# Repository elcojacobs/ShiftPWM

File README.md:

# ShiftPWM-Redux
Arduino Library for software PWM with shift registers

This branch optimizes the SPI sending code. 

The new code is about 30% faster than the original. You can use the extra time to either have more foreground load, or to increase the PWM frequency.

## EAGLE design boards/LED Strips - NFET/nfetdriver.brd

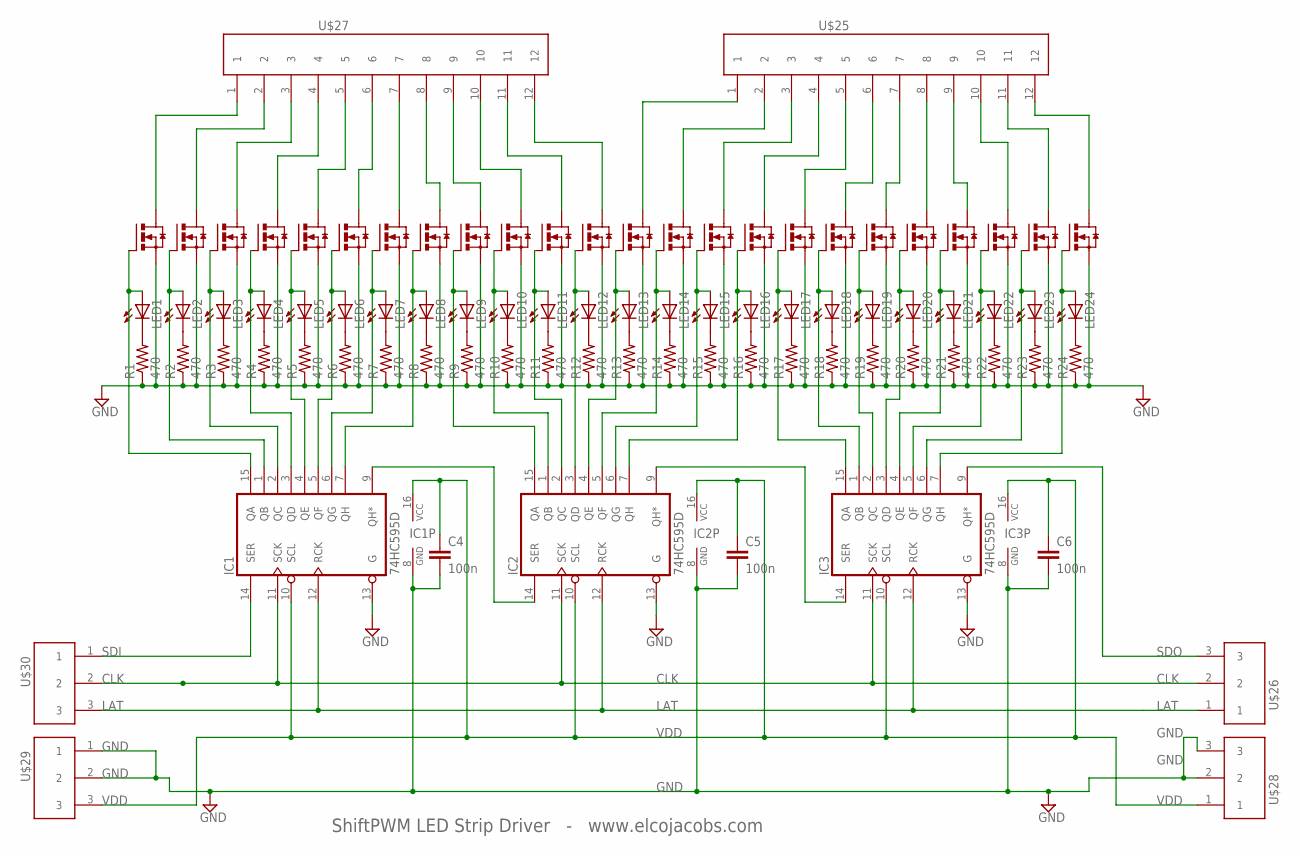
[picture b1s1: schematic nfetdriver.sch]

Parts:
C4, C5, C6: 100n; C0603
IC1, IC2, IC3: 74HC595D; SO16
LED1, LED2, LED3, LED4, LED5, LED6, LED7, LED8, LED9, LED10, LED11, LED12, LED13, LED14, LED15, LED16, LED17, LED18, LED19, LED20, LED21, LED22, LED23, LED24: LEDCHIPLED_0603; CHIPLED_0603
R1, R2, R3, R4, R5, R6, R7, R8, R9, R10, R11, R12, R13, R14, R15, R16, R17, R18, R19, R20, R21, R22, R23, R24: 470; R0603
U$1, U$2, U$3, U$4, U$5, U$6, U$7, U$8, U$9, U$10, U$11, U$12, U$13, U$14, U$15, U$16, U$17, U$18, U$19, U$20, U$21, U$22, U$23, U$24: SI2302DS; SOT23
U$25, U$27: 3.5MM12P
U$26, U$28, U$29, U$30: 3.5MM3PHORIZONTAL; 3.5MM3P

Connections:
CLK: IC1.11 (SCK), IC2.11 (SCK), IC3.11 (SCK), U$26.2, U$30.2
GND: C4.2, C5.2, C6.2, IC1.8 (GND), IC1.13 (G), IC2.8 (GND), IC2.13 (G), IC3.8 (GND), IC3.13 (G), R1.1, R2.1, R3.1, R4.1, R5.1, R6.1, R7.1, R8.1, R9.1, R10.1, R11.1, R12.1, R13.1, R14.1, R15.1, R16.1, R17.1, R18.1, R19.1, R20.1, R21.1, R22.1, R23.1, R24.1, U$1.SOURCE (S), U$2.SOURCE (S), U$3.SOURCE (S), U$4.SOURCE (S), U$5.SOURCE (S), U$6.SOURCE (S), U$7.SOURCE (S), U$8.SOURCE (S), U$9.SOURCE (S), U$10.SOURCE (S), U$11.SOURCE (S), U$12.SOURCE (S), U$13.SOURCE (S), U$14.SOURCE (S), U$15.SOURCE (S), U$16.SOURCE (S), U$17.SOURCE (S), U$18.SOURCE (S), U$19.SOURCE (S), U$20.SOURCE (S), U$21.SOURCE (S), U$22.SOURCE (S), U$23.SOURCE (S), U$24.SOURCE (S), U$28.2, U$28.3, U$29.1, U$29.2
LAT: IC1.12 (RCK), IC2.12 (RCK), IC3.12 (RCK), U$26.1, U$30.3
unnamed: IC1.9 (QH*), IC2.14 (SER)
unnamed: IC2.9 (QH*), IC3.14 (SER)
unnamed: IC1.15 (QA), LED1.A, U$1.GATE (G)
unnamed: IC1.1 (QB), LED2.A, U$2.GATE (G)
unnamed: IC1.2 (QC), LED3.A, U$3.GATE (G)
unnamed: IC1.3 (QD), LED4.A, U$4.GATE (G)
unnamed: IC1.4 (QE), LED5.A, U$5.GATE (G)
unnamed: IC1.6 (QG), LED7.A, U$7.GATE (G)
unnamed: IC1.5 (QF), LED6.A, U$6.GATE (G)
unnamed: U$1.DRAIN (D), U$27.1
unnamed: IC2.15 (QA), LED9.A, U$9.GATE (G)
unnamed: IC2.1 (QB), LED10.A, U$10.GATE (G)
unnamed: IC2.2 (QC), LED11.A, U$11.GATE (G)
unnamed: IC2.3 (QD), LED12.A, U$12.GATE (G)
unnamed: IC2.4 (QE), LED13.A, U$13.GATE (G)
unnamed: IC2.5 (QF), LED14.A, U$14.GATE (G)
unnamed: IC2.6 (QG), LED15.A, U$15.GATE (G)
unnamed: IC2.7 (QH), LED16.A, U$16.GATE (G)
unnamed: IC3.15 (QA), LED17.A, U$17.GATE (G)
unnamed: IC3.1 (QB), LED18.A, U$18.GATE (G)
unnamed: IC3.2 (QC), LED19.A, U$19.GATE (G)
unnamed: IC3.3 (QD), LED20.A, U$20.GATE (G)
unnamed: IC3.4 (QE), LED21.A, U$21.GATE (G)
unnamed: IC3.5 (QF), LED22.A, U$22.GATE (G)
unnamed: IC3.6 (QG), LED23.A, U$23.GATE (G)
unnamed: IC3.7 (QH), LED24.A, U$24.GATE (G)
unnamed: U$2.DRAIN (D), U$27.2
unnamed: U$3.DRAIN (D), U$27.3
unnamed: U$4.DRAIN (D), U$27.4
unnamed: U$5.DRAIN (D), U$27.5
unnamed: U$6.DRAIN (D), U$27.6
unnamed: U$7.DRAIN (D), U$27.7
unnamed: U$8.DRAIN (D), U$27.8
unnamed: U$9.DRAIN (D), U$27.9
unnamed: U$10.DRAIN (D), U$27.10
unnamed: U$11.DRAIN (D), U$27.11
unnamed: U$12.DRAIN (D), U$27.12
unnamed: U$13.DRAIN (D), U$25.1
unnamed: U$14.DRAIN (D), U$25.2
unnamed: IC1.7 (QH), LED8.A, U$8.GATE (G)
unnamed: U$16.DRAIN (D), U$25.4
unnamed: U$17.DRAIN (D), U$25.5
unnamed: U$18.DRAIN (D), U$25.6
unnamed: U$19.DRAIN (D), U$25.7
unnamed: U$20.DRAIN (D), U$25.8
unnamed: U$21.DRAIN (D), U$25.9
unnamed: U$22.DRAIN (D), U$25.10
unnamed: U$23.DRAIN (D), U$25.11
unnamed: U$24.DRAIN (D), U$25.12
unnamed: LED1.C, R1.2
unnamed: LED2.C, R2.2
unnamed: LED3.C, R3.2
unnamed: LED4.C, R4.2
unnamed: LED5.C, R5.2
unnamed: LED6.C, R6.2
unnamed: LED7.C, R7.2
unnamed: LED8.C, R8.2
unnamed: LED9.C, R9.2
unnamed: LED10.C, R10.2
unnamed: LED11.C, R11.2
unnamed: LED12.C, R12.2
unnamed: LED13.C, R13.2
unnamed: LED14.C, R14.2
unnamed: LED15.C, R15.2
unnamed: LED16.C, R16.2
unnamed: LED17.C, R17.2
unnamed: LED18.C, R18.2
unnamed: LED19.C, R19.2
unnamed: LED20.C, R20.2
unnamed: LED21.C, R21.2
unnamed: LED22.C, R22.2
unnamed: LED23.C, R23.2
unnamed: LED24.C, R24.2
unnamed: U$15.DRAIN (D), U$25.3
SDI: IC1.14 (SER), U$30.1
SDO: IC3.9 (QH*), U$26.3
VDD: C4.1, C5.1, C6.1, IC1.10 (SCL), IC1.16 (VCC), IC2.10 (SCL), IC2.16 (VCC), IC3.10 (SCL), IC3.16 (VCC), U$28.1, U$29.3

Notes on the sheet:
ShiftPWM LED Strip Driver - www.elcojacobs.com
SDI
SDO
VDD

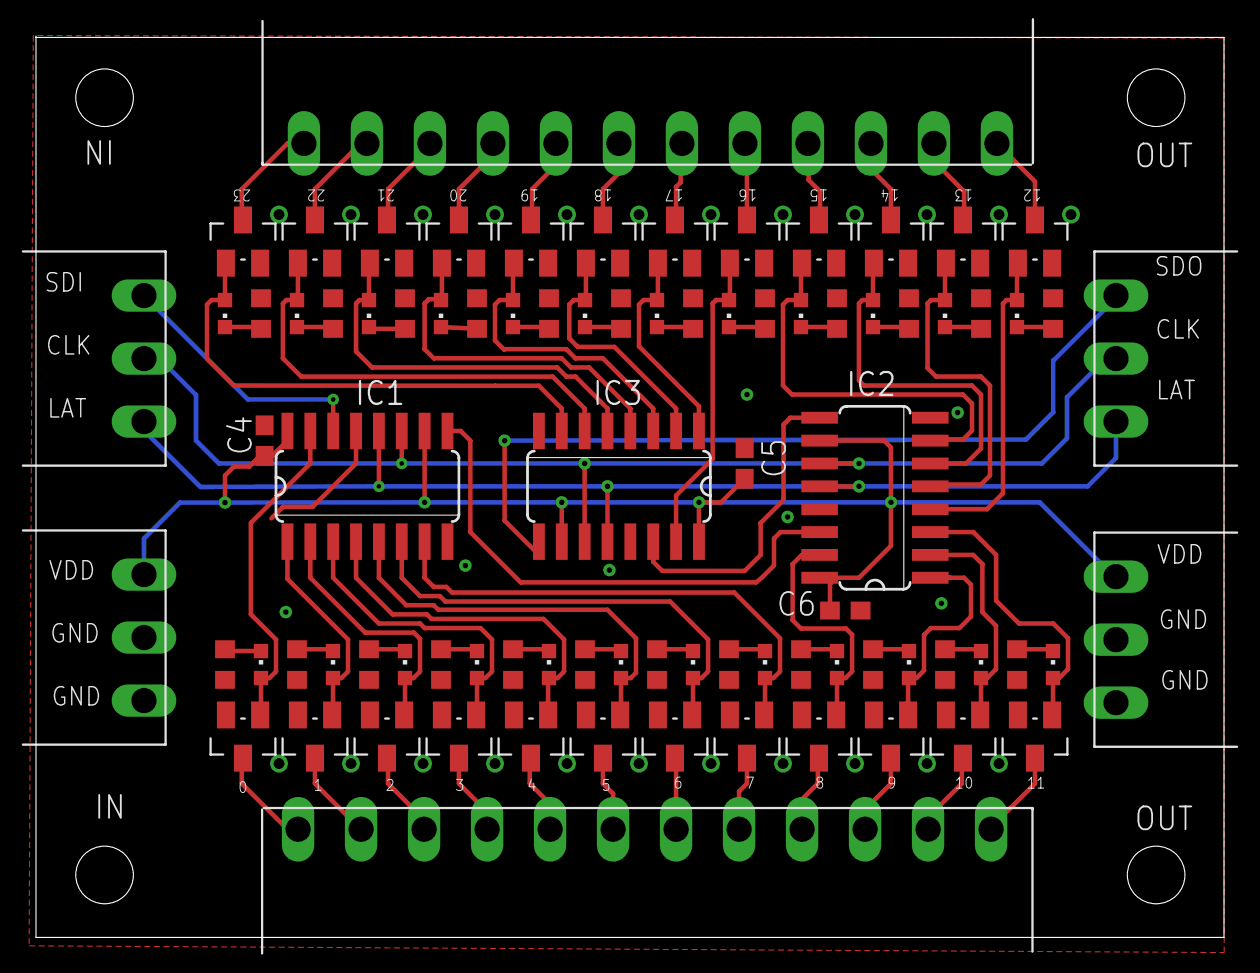
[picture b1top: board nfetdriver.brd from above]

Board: 2 copper layers, 66.0 x 50.0 mm, 84 parts (0 on the bottom side), 80 nets.

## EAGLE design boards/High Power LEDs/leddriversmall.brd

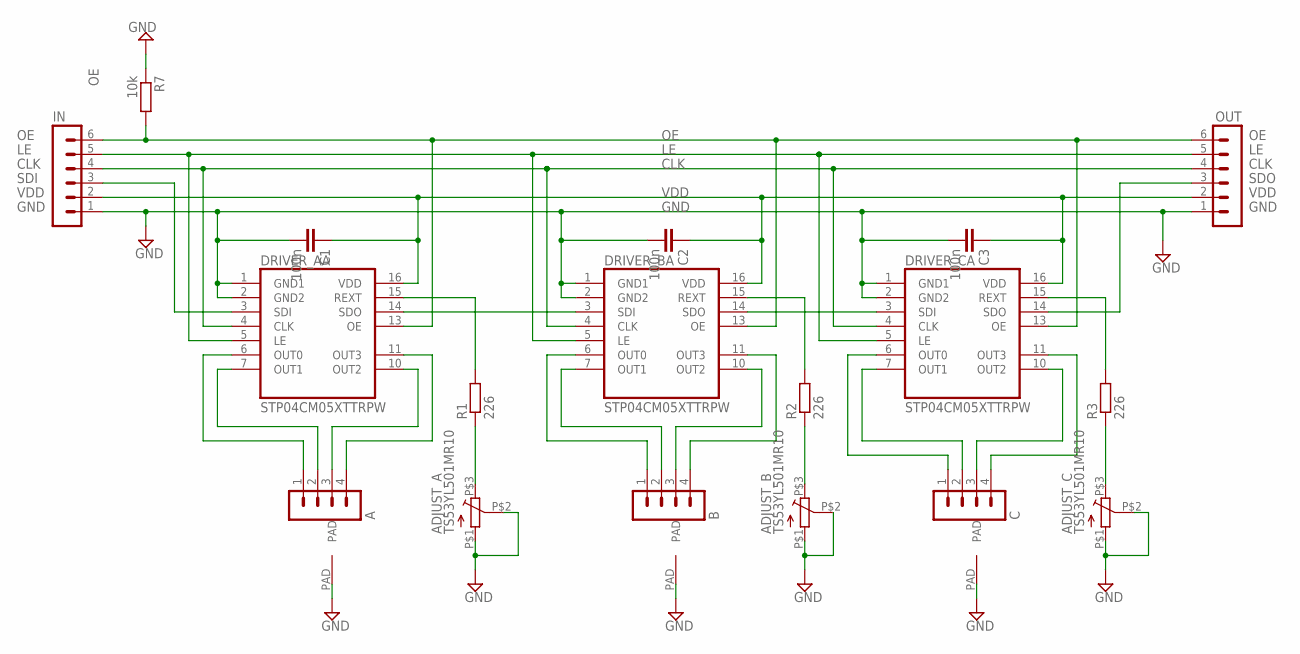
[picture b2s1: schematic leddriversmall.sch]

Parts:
A: MA04-1
ADJUST_A: TS53YL501MR10; TS53Y
ADJUST_B: TS53YL501MR10; TS53Y
ADJUST_C: TS53YL501MR10; TS53Y
B: MA04-1
C: MA04-1
C1, C2, C3: 100n; C0805
DRIVER_A: STP04CM05XTTRPW; HTSSOP16
DRIVER_B: STP04CM05XTTRPW; HTSSOP16
DRIVER_C: STP04CM05XTTRPW; HTSSOP16
IN: MA06-1
OUT: MA06-1
R1, R2, R3: 226; R0805
R7: 10k; R0805

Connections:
CLK: DRIVER_A.4 (CLK), DRIVER_B.4 (CLK), DRIVER_C.4 (CLK), IN.4, OUT.4
GND: ADJUST_A.P$1 (A), ADJUST_A.P$2 (B), ADJUST_B.P$1 (A), ADJUST_B.P$2 (B), ADJUST_C.P$1 (A), ADJUST_C.P$2 (B), C1.2, C2.2, C3.2, DRIVER_A.1 (GND1), DRIVER_A.2 (GND2), DRIVER_A.PAD, DRIVER_B.1 (GND1), DRIVER_B.2 (GND2), DRIVER_B.PAD, DRIVER_C.1 (GND1), DRIVER_C.2 (GND2), DRIVER_C.PAD, IN.1, OUT.1, R7.1
LE: DRIVER_A.5 (LE), DRIVER_B.5 (LE), DRIVER_C.5 (LE), IN.5, OUT.5
unnamed: DRIVER_A.14 (SDO), DRIVER_B.3 (SDI)
unnamed: DRIVER_B.14 (SDO), DRIVER_C.3 (SDI)
unnamed: ADJUST_A.P$3 (C), R1.1
unnamed: ADJUST_B.P$3 (C), R2.1
unnamed: ADJUST_C.P$3 (C), R3.1
unnamed: A.4, DRIVER_A.11 (OUT3)
unnamed: B.1, DRIVER_B.6 (OUT0)
unnamed: A.1, DRIVER_A.6 (OUT0)
unnamed: C.2, DRIVER_C.7 (OUT1)
unnamed: A.3, DRIVER_A.10 (OUT2)
unnamed: B.2, DRIVER_B.7 (OUT1)
unnamed: A.2, DRIVER_A.7 (OUT1)
unnamed: C.3, DRIVER_C.10 (OUT2)
unnamed: C.4, DRIVER_C.11 (OUT3)
unnamed: C.1, DRIVER_C.6 (OUT0)
unnamed: B.3, DRIVER_B.10 (OUT2)
unnamed: DRIVER_A.15 (REXT), R1.2
unnamed: B.4, DRIVER_B.11 (OUT3)
unnamed: DRIVER_B.15 (REXT), R2.2
OE: DRIVER_A.13 (OE), DRIVER_B.13 (OE), DRIVER_C.13 (OE), IN.6, OUT.6, R7.2
REXT: DRIVER_C.15 (REXT), R3.2
SDI: DRIVER_A.3 (SDI), IN.3
SDO: DRIVER_C.14 (SDO), OUT.3
VDD: C1.1, C2.1, C3.1, DRIVER_A.16 (VDD), DRIVER_B.16 (VDD), DRIVER_C.16 (VDD), IN.2, OUT.2

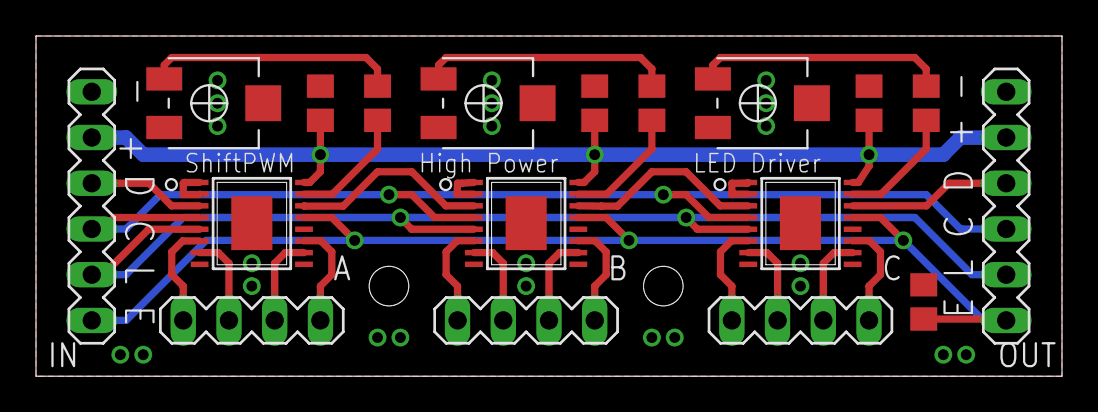
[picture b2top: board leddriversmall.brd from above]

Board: 2 copper layers, 57.0 x 18.9 mm, 18 parts (0 on the bottom side), 27 nets.

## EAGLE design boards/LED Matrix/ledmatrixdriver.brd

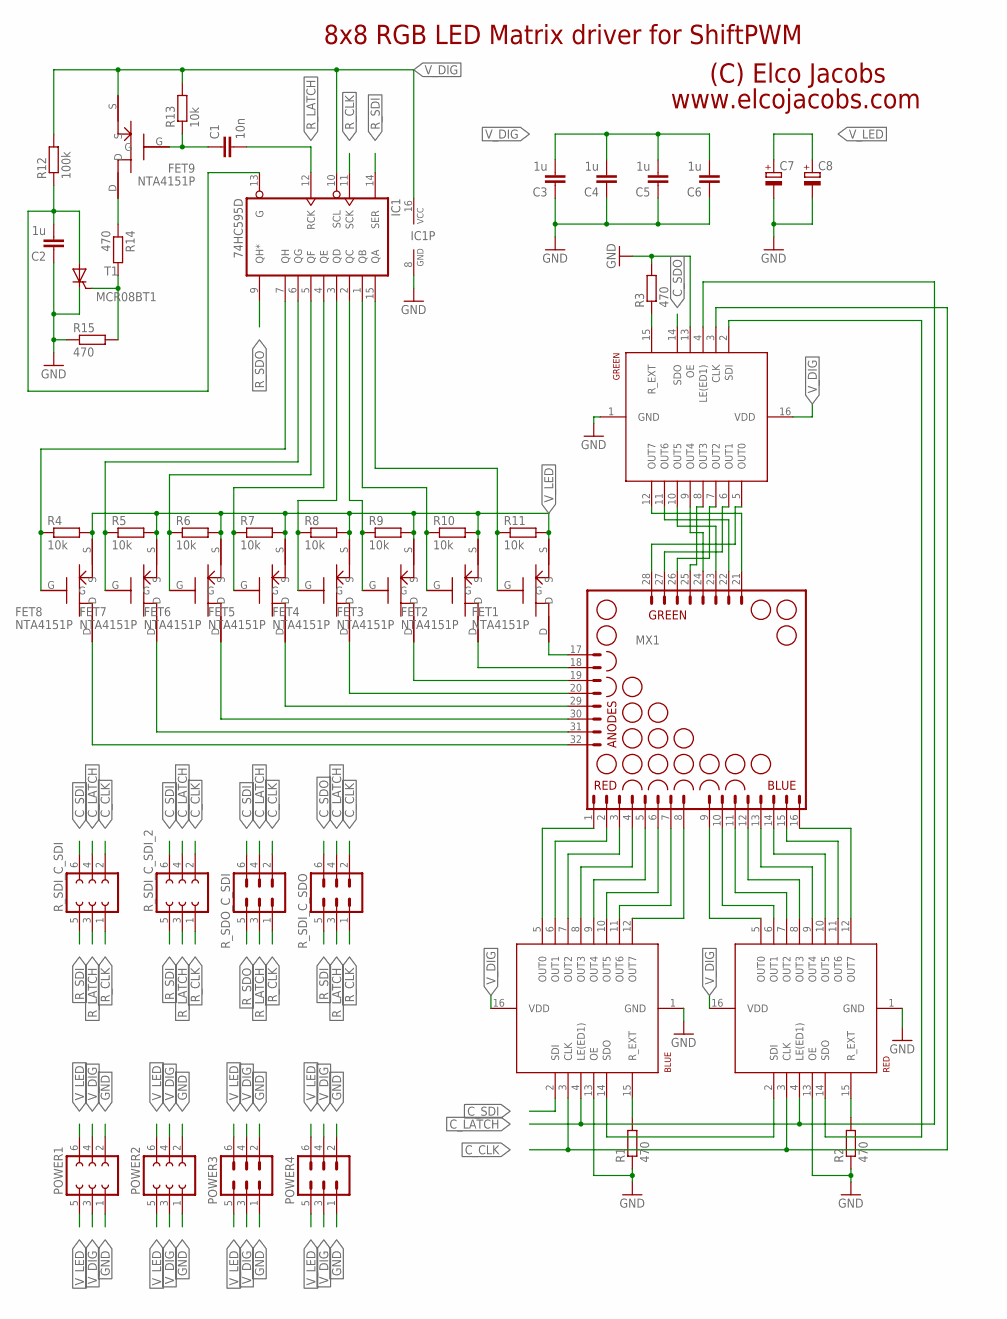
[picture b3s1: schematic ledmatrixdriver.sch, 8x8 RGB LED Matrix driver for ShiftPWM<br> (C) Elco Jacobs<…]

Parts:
BLUE: TLC5916; SOIC-16
C1: 10n; C0805
C2, C3, C4, C5, C6: 1u; C0805
C7, C8: CPOL-EU153CLV-0505; 153CLV-0505
FET1, FET2, FET3, FET4, FET5, FET6, FET7, FET8, FET9: NTA4151P
GREEN: TLC5916; SOIC-16
IC1: 74HC595D; SO16
MX1: MATRIX_8X8_TRICOLOR_ANODE_ROW; MATRIX_60MM_32PIN
POWER1, POWER2: FE03-2W
POWER3, POWER4: MA03-2W
R1, R2, R3, R14, R15: 470; R0805
R4, R5, R6, R7, R8, R9, R10, R11, R13: 10k; R0402
R12: 100k; R0805
RED: TLC5916; SOIC-16
R_SDI_C_SDI: FE03-2W
R_SDI_C_SDI_2: FE03-2W
R_SDI_C_SDO: MA03-2W
R_SDO_C_SDI: MA03-2W
T1: MCR08BT1; SOT223

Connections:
C_CLK: BLUE.3 (CLK), GREEN.3 (CLK), RED.3 (CLK), R_SDI_C_SDI.2, R_SDI_C_SDI_2.2, R_SDI_C_SDO.2, R_SDO_C_SDI.2
C_LATCH: BLUE.4 (LE(ED1)), GREEN.4 (LE(ED1)), RED.4 (LE(ED1)), R_SDI_C_SDI.4, R_SDI_C_SDI_2.4, R_SDI_C_SDO.4, R_SDO_C_SDI.4
C_SDI: BLUE.2 (SDI), R_SDI_C_SDI.6, R_SDI_C_SDI_2.6, R_SDO_C_SDI.6
C_SDO: GREEN.14 (SDO), R_SDI_C_SDO.6
GND: BLUE.1 (GND), BLUE.13 (OE), C2.1, C3.1, C4.1, C5.1, C6.1, C7.-, C8.-, GREEN.1 (GND), GREEN.13 (OE), IC1.8 (GND), POWER1.1, POWER1.2, POWER2.1, POWER2.2, POWER3.1, POWER3.2, POWER4.1, POWER4.2, R1.1, R2.1, R3.2, R15.1, RED.1 (GND), RED.13 (OE), T1.K (C)
unnamed: BLUE.5 (OUT0), MX1.1
unnamed: BLUE.6 (OUT1), MX1.2
unnamed: BLUE.7 (OUT2), MX1.3
unnamed: BLUE.8 (OUT3), MX1.4
unnamed: BLUE.9 (OUT4), MX1.5
unnamed: BLUE.10 (OUT5), MX1.6
unnamed: BLUE.11 (OUT6), MX1.7
unnamed: BLUE.12 (OUT7), MX1.8
unnamed: MX1.10, RED.6 (OUT1)
unnamed: MX1.11, RED.7 (OUT2)
unnamed: MX1.12, RED.8 (OUT3)
unnamed: MX1.13, RED.9 (OUT4)
unnamed: MX1.14, RED.10 (OUT5)
unnamed: MX1.15, RED.11 (OUT6)
unnamed: MX1.16, RED.12 (OUT7)
unnamed: GREEN.12 (OUT7), MX1.21
unnamed: GREEN.11 (OUT6), MX1.22
unnamed: GREEN.10 (OUT5), MX1.23
unnamed: GREEN.9 (OUT4), MX1.24
unnamed: GREEN.8 (OUT3), MX1.25
unnamed: GREEN.7 (OUT2), MX1.26
unnamed: GREEN.6 (OUT1), MX1.27
unnamed: GREEN.5 (OUT0), MX1.28
unnamed: FET1.D, MX1.17
unnamed: FET2.D, MX1.18
unnamed: FET3.D, MX1.19
unnamed: FET4.D, MX1.20
unnamed: FET5.D, MX1.29
unnamed: FET6.D, MX1.30
unnamed: FET7.D, MX1.31
unnamed: FET8.D, MX1.32
unnamed: FET1.G, IC1.15 (QA), R11.1
unnamed: FET2.G, IC1.1 (QB), R10.1
unnamed: FET3.G, IC1.2 (QC), R9.1
unnamed: FET4.G, IC1.3 (QD), R8.1
unnamed: FET5.G, IC1.4 (QE), R7.1
unnamed: FET6.G, IC1.5 (QF), R6.1
unnamed: FET7.G, IC1.6 (QG), R5.1
unnamed: C2.2, IC1.13 (G), R12.1, T1.A, T1.A2 (A)
unnamed: BLUE.15 (R_EXT), R1.2
unnamed: R2.2, RED.15 (R_EXT)
unnamed: GREEN.15 (R_EXT), R3.1
unnamed: BLUE.14 (SDO), RED.2 (SDI)
unnamed: FET9.D, R14.1
unnamed: R14.2, R15.2, T1.G
unnamed: GREEN.2 (SDI), RED.14 (SDO)
unnamed: C1.1, FET9.G, R13.1
OUT0B: MX1.9, RED.5 (OUT0)
QH: FET8.G, IC1.7 (QH), R4.1
R_CLK: IC1.11 (SCK), R_SDI_C_SDI.1, R_SDI_C_SDI_2.1, R_SDI_C_SDO.1, R_SDO_C_SDI.1
R_LATCH: C1.2, IC1.12 (RCK), R_SDI_C_SDI.3, R_SDI_C_SDI_2.3, R_SDI_C_SDO.3, R_SDO_C_SDI.3
R_SDI: IC1.14 (SER), R_SDI_C_SDI.5, R_SDI_C_SDI_2.5, R_SDI_C_SDO.5
R_SDO: IC1.9 (QH*), R_SDO_C_SDI.5
V_DIG: BLUE.16 (VDD), C3.2, C4.2, C5.2, C6.2, FET9.S, GREEN.16 (VDD), IC1.10 (SCL), IC1.16 (VCC), POWER1.3, POWER1.4, POWER2.3, POWER2.4, POWER3.3, POWER3.4, POWER4.3, POWER4.4, R12.2, R13.2, RED.16 (VDD)
V_LED: C7.+, C8.+, FET1.S, FET2.S, FET3.S, FET4.S, FET5.S, FET6.S, FET7.S, FET8.S, POWER1.5, POWER1.6, POWER2.5, POWER2.6, POWER3.5, POWER3.6, POWER4.5, POWER4.6, R4.2, R5.2, R6.2, R7.2, R8.2, R9.2, R10.2, R11.2

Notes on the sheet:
8x8 RGB LED Matrix driver for ShiftPWM
(C) Elco Jacobs
www.elcojacobs.com

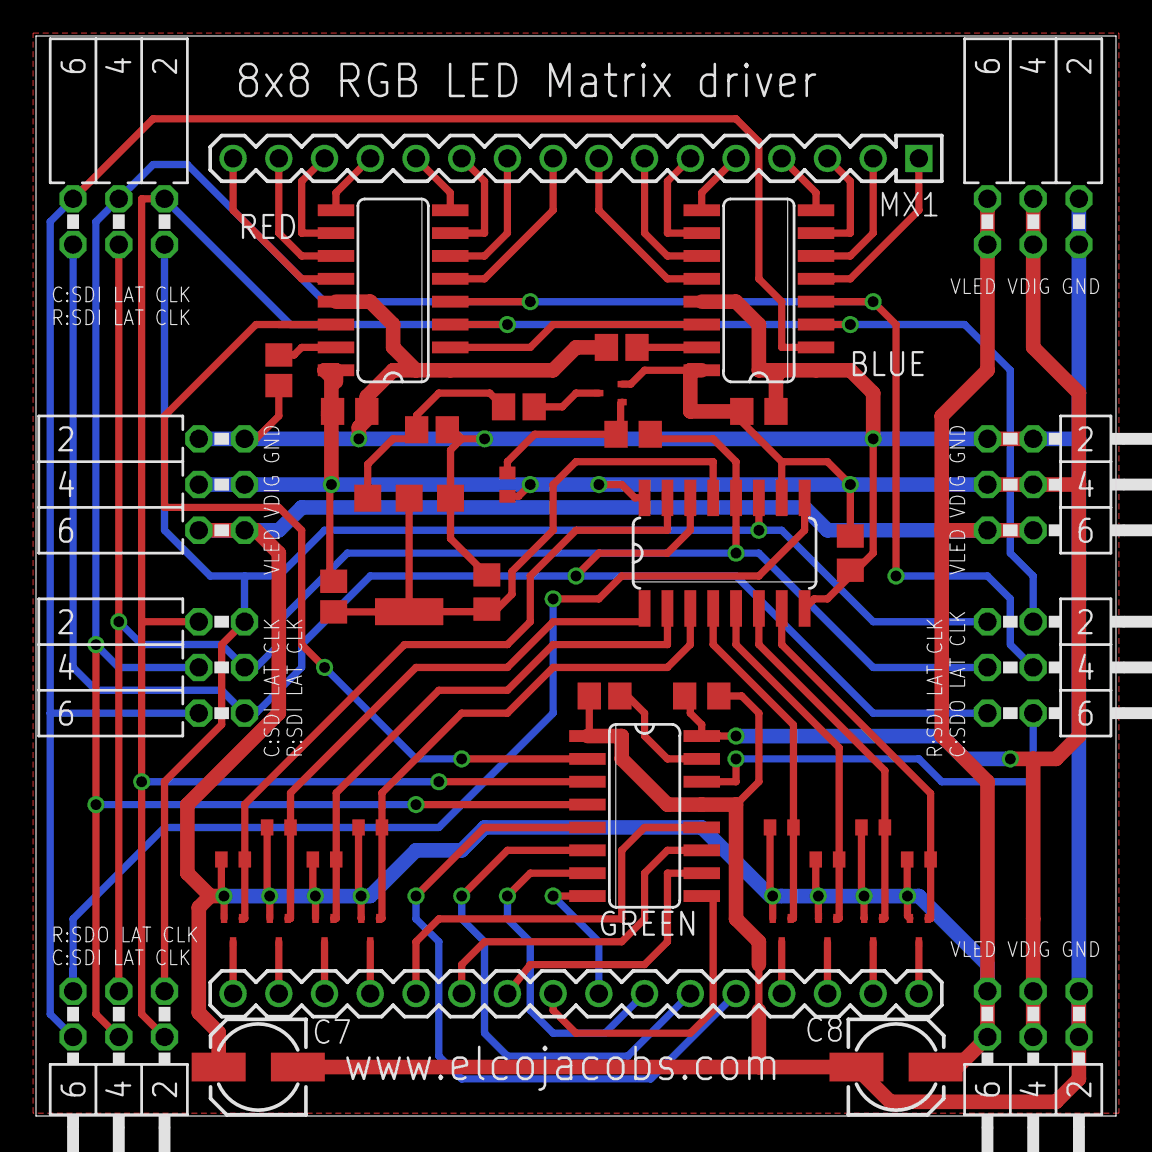
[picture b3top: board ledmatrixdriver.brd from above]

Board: 2 copper layers, 60.0 x 60.0 mm, 46 parts (0 on the bottom side), 60 nets.

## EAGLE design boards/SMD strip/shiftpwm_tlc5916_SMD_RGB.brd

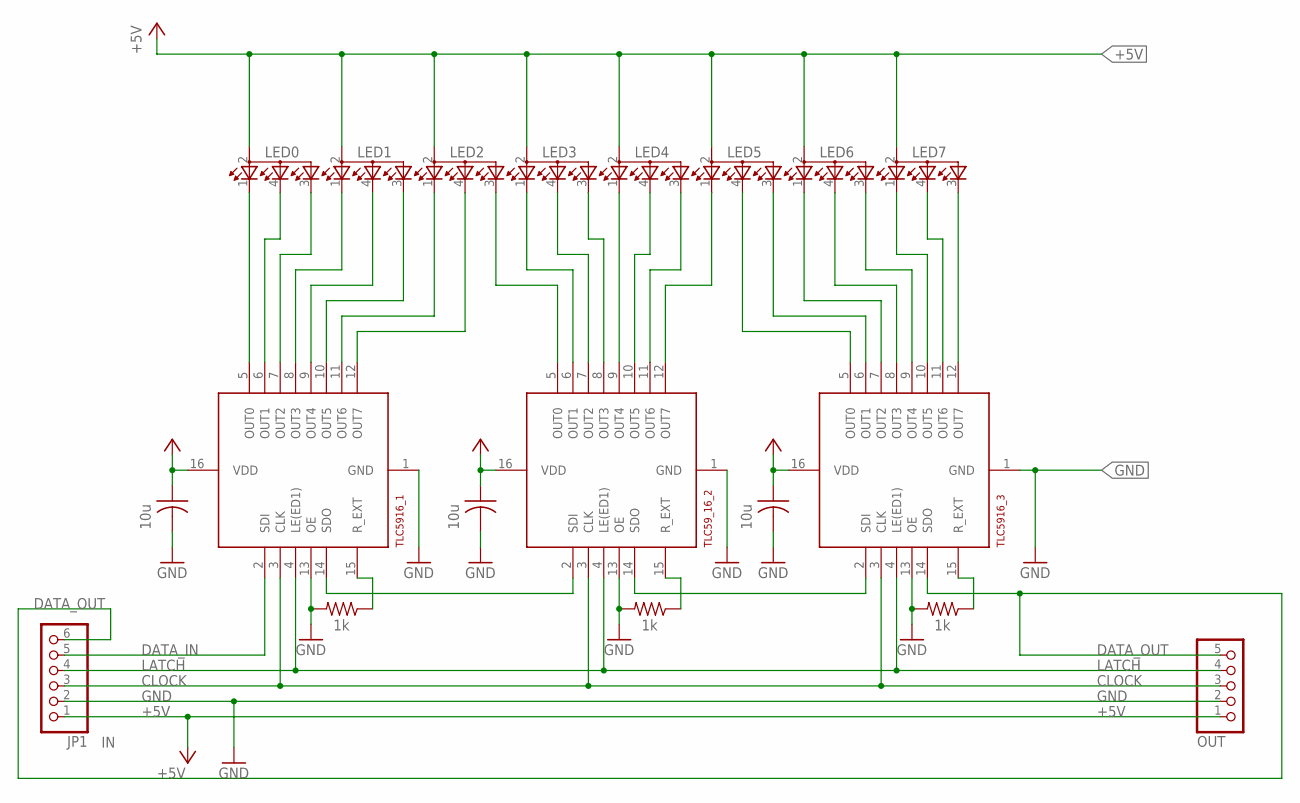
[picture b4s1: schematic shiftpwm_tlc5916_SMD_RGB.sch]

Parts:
C1, C2, C3: 10u; C0805K
JP1: IN; 1X06
LED0, LED1, LED2, LED3, LED4, LED5, LED6, LED7: PLLC4-RGB-ELCOSMALL; P-LCC-4-3-ELCO
OUT: PINHD-1X5; 1X05
R1, R2, R3: 1k; R0805
TLC59_16_2, TLC5916_1, TLC5916_3: TLC5916/17; SOIC-16

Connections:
+5V: C1.1, C2.1, C3.1, JP1.1, LED0.2 (A2), LED1.2 (A2), LED2.2 (A2), LED3.2 (A2), LED4.2 (A2), LED5.2 (A2), LED6.2 (A2), LED7.2 (A2), OUT.1, TLC59_16_2.16 (VDD), TLC5916_1.16 (VDD), TLC5916_3.16 (VDD)
CLOCK: JP1.3, OUT.3, TLC59_16_2.3 (CLK), TLC5916_1.3 (CLK), TLC5916_3.3 (CLK)
DATA_IN: JP1.5, TLC5916_1.2 (SDI)
DATA_OUT: JP1.6, OUT.5, TLC5916_3.14 (SDO)
GND: C1.2, C2.2, C3.2, JP1.2, OUT.2, R1.2, R2.2, R3.2, TLC59_16_2.1 (GND), TLC59_16_2.13 (OE), TLC5916_1.1 (GND), TLC5916_1.13 (OE), TLC5916_3.1 (GND), TLC5916_3.13 (OE)
LATCH: JP1.4, OUT.4, TLC59_16_2.4 (LE(ED1)), TLC5916_1.4 (LE(ED1)), TLC5916_3.4 (LE(ED1))
unnamed: TLC59_16_2.14 (SDO), TLC5916_3.2 (SDI)
unnamed: R2.1, TLC59_16_2.15 (R_EXT)
unnamed: R1.1, TLC5916_1.15 (R_EXT)
unnamed: TLC59_16_2.2 (SDI), TLC5916_1.14 (SDO)
unnamed: LED7.3 (CBLUE), TLC5916_3.12 (OUT7)
unnamed: R3.1, TLC5916_3.15 (R_EXT)
unnamed: LED0.1 (CRED), TLC5916_1.5 (OUT0)
unnamed: LED0.4 (CGREEN), TLC5916_1.6 (OUT1)
unnamed: LED0.3 (CBLUE), TLC5916_1.7 (OUT2)
unnamed: LED1.1 (CRED), TLC5916_1.8 (OUT3)
unnamed: LED1.4 (CGREEN), TLC5916_1.9 (OUT4)
unnamed: LED1.3 (CBLUE), TLC5916_1.10 (OUT5)
unnamed: LED2.1 (CRED), TLC5916_1.11 (OUT6)
unnamed: LED2.4 (CGREEN), TLC5916_1.12 (OUT7)
unnamed: LED2.3 (CBLUE), TLC59_16_2.5 (OUT0)
unnamed: LED3.1 (CRED), TLC59_16_2.6 (OUT1)
unnamed: LED3.4 (CGREEN), TLC59_16_2.7 (OUT2)
unnamed: LED3.3 (CBLUE), TLC59_16_2.8 (OUT3)
unnamed: LED4.1 (CRED), TLC59_16_2.9 (OUT4)
unnamed: LED4.4 (CGREEN), TLC59_16_2.10 (OUT5)
unnamed: LED4.3 (CBLUE), TLC59_16_2.11 (OUT6)
unnamed: LED5.1 (CRED), TLC59_16_2.12 (OUT7)
unnamed: LED7.4 (CGREEN), TLC5916_3.11 (OUT6)
unnamed: LED7.1 (CRED), TLC5916_3.10 (OUT5)
unnamed: LED6.3 (CBLUE), TLC5916_3.9 (OUT4)
unnamed: LED6.4 (CGREEN), TLC5916_3.8 (OUT3)
unnamed: LED6.1 (CRED), TLC5916_3.7 (OUT2)
unnamed: LED5.3 (CBLUE), TLC5916_3.6 (OUT1)
unnamed: LED5.4 (CGREEN), TLC5916_3.5 (OUT0)

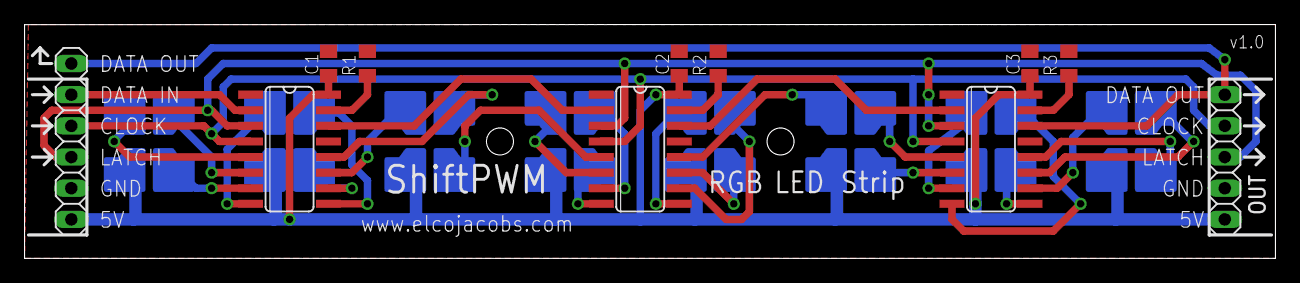
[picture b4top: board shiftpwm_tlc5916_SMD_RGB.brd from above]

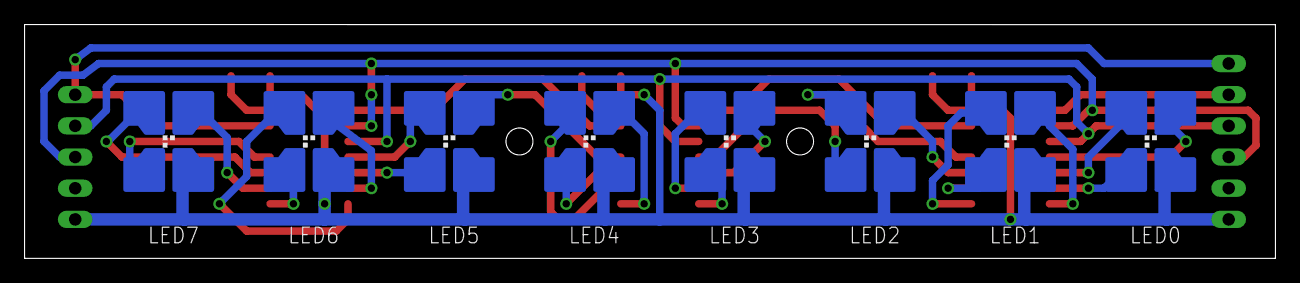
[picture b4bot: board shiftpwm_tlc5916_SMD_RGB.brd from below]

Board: 2 copper layers, 101.9 x 19.1 mm, 19 parts (8 on the bottom side), 35 nets.

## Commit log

2012-05-05 First commit on Git, corresponds to Google Code version 1.04
2012-05-05 Used the F() function to move constant strings to PROGMEM. This saves RAM.
2012-05-06 Integrated RGB and HSV functions into the library. Added an example with random updates, some hue fading and a VU meter demo.
2012-05-07 Added optional offset argument to SetGroupOf#, SetRGB and SetHSV functions. Default value is zero, so argument can be omitted.
    This is useful, for example, if you have chained 2 boards together each with 4 registers: 10 RGB LED's and 2 unused pins per board.
    You can now set LED's on the second board with:
    SetRGB(11,255,0,255,2); // Set first LED of the second board to purple.
2012-05-07 Added SetPinGrouping(). This function gives you flexibility in led setup. If you use RRRRGGGGBBBB... use SetPinGrouping(4).
    Updated other functions to use this value.
    Updated keywords file (use tabs instead of spaces)
    Changed some member variable names that did not have the m_ prefix
2012-05-09 Added support for using ShiftPWM without the SPI port.
2012-05-09 added keyword for NOSPI
2012-05-09 Added newline characters at end of files
2012-07-08 Fixed bug in SetAllHSV function
2012-07-08 - Added a new example for non blocking fades, which responds to serial port commands to set the fading mode - Changed the default setting to non-inverting - Changed the default setting for the noSPI 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
2012-07-12 maxBrightness+1 instead of maxBrightness in LoadNotTooHigh()
2012-08-09 - Moved pins and SPI initialization into library. - Rewrote examples, so that one version can be used for SPI and non-SPI. - Added load balancing - Updated comments
2012-08-09 Added Leonardo compatibility
2012-08-15 Missing 'bool' in variable declaration for load balancing
2012-09-29 Added gitignore and gitattributes
2012-10-05 Minor changes to make it compatible with Atmel Studio
2012-12-06 Improved compatibility with the Atmega32u4 (Leonardo/Micro) and Arduino 1.02
2012-12-07 Corrected an error in previous commit, causing compile erros when using the default timer1 on the UNO
2014-06-09 Begin non-AVR porting
2014-06-09 Finish porting to Teensy 3.1
2015-01-22 Open sourced all hardware. I do not have time to offer support. Files are provided as is, no warranty.
2015-12-20 Working SPI ISR optimizations with ~30% performance improvement and no functional changes
    Replaced the existing loop enclosing a sequence of 8 calls to
    add_one_pin_to_byte() with the singe function send_spi_bytes(). Writing
    the whole send sequence in a single inline ASM allowed for pre-decrement
    indexing and some other smaller optimization in count checking and bit
    inversion.
2016-01-19 Support Teensy LC
2016-12-24 Fix compiler warnings
2017-03-15 Bitbang delays to pmeet HC595 timing with faster Teensy 3.x
2020-05-27 Add MIT license
